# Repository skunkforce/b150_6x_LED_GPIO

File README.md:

# edgy_board number b150
This design is part of the [edgy board project](https://github.com/skunkforce/edgy_boards).

# getting started
This repository uses submodules. After cloning use the command 

```$ git submodule update --init --recursive```

to pull the submodules before opening the project with kicad. 

# Tests
Tests can be found in [TESTS.md](TESTS.md)

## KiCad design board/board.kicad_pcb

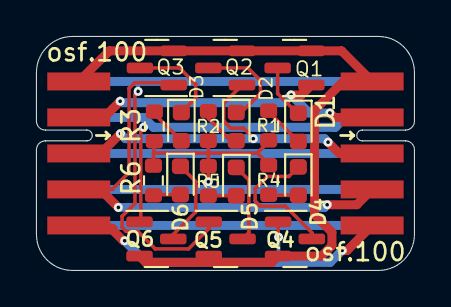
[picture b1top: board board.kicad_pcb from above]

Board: 2 copper layers, 21.0 x 13.0 mm, 21 parts (1 on the bottom side), 22 nets.

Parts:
D1, D2, D3, D4, D5, D6: LED; LED_0603_1608Metric
J1: 011_GPIO; on_edge_2x05_host
J2: 011_GPIO; on_edge_2x05_device
LOGO1: Logo_Open_Hardware_Small; OSHW-Symbol_6.7x6mm_SilkScreen
Q1, Q2, Q3, Q4, Q5, Q6: 2N7002K; SOT-23
R1, R2, R3, R4, R5, R6: 100R; R_0603_1608Metric

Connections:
GND: J1.1 (GND), J2.1 (GND), Q1.2 (S), Q2.2 (S), Q3.2 (S), Q4.2 (S), Q5.2 (S), Q6.2 (S)
unnamed: D1.2 (A), R1.2
unnamed: D1.1 (K), Q1.3 (D)
unnamed: D2.2 (A), R2.2
unnamed: D2.1 (K), Q2.3 (D)
unnamed: D3.2 (A), R3.2
unnamed: D3.1 (K), Q3.3 (D)
unnamed: D4.2 (A), R4.2
unnamed: D4.1 (K), Q4.3 (D)
unnamed: D5.2 (A), R5.2
unnamed: D5.1 (K), Q5.3 (D)
unnamed: D6.2 (A), R6.2
unnamed: D6.1 (K), Q6.3 (D)
unnamed: J1.9 (3.3V), J2.9 (3.3V), R1.1, R2.1, R3.1, R4.1, R5.1, R6.1
unnamed: J1.10 (5V), J2.10 (5V)
unnamed: J1.8 (GND), J2.8 (GND)
unnamed: J1.2 (GPIO0), J2.2 (GPIO0), Q1.1 (G)
unnamed: J1.3 (GPIO1), J2.3 (GPIO1), Q2.1 (G)
unnamed: J1.4 (GPIO2), J2.4 (GPIO2), Q3.1 (G)
unnamed: J1.5 (GPIO3), J2.5 (GPIO3), Q4.1 (G)
unnamed: J1.6 (GPIO4), J2.6 (GPIO4), Q5.1 (G)
unnamed: J1.7 (GPIO5), J2.7 (GPIO5), Q6.1 (G)

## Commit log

2024-01-14 initial
